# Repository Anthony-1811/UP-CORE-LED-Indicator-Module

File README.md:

# UP CORE LED Indicator module
A quick little PCB to get an LED indicatior on your Up Core. Just send it a string on UART0 on the Up Core.

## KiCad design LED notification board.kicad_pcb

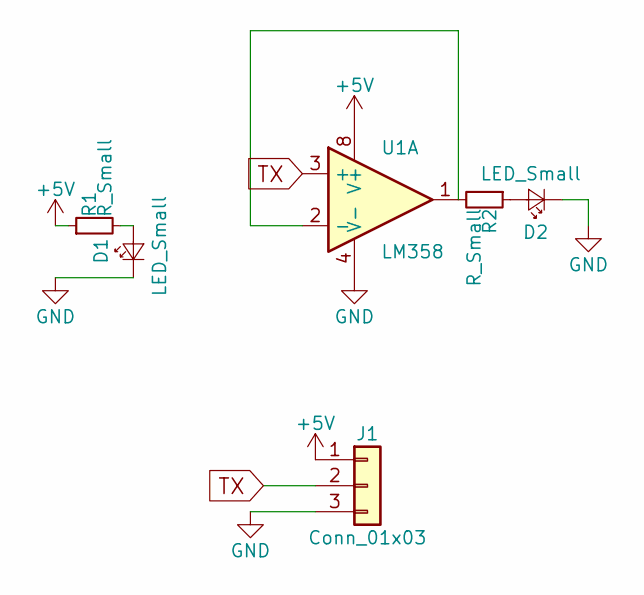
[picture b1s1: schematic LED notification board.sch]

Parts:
D1, D2: LED_Small; LED_0805_HandSoldering
J1: Conn_01x03; JST_GH_SM03B-GHS-TB_03x1.25mm_Angled
R1, R2: R_Small; R_0805_HandSoldering
U1: LM358; SOIC-8_3.9x4.9mm_Pitch1.27mm

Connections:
+5V: J1.1, R1.1, U1.8 (V+)
GND: D1.1 (K), D2.1 (K), J1.3, U1.4 (V-)
unnamed: D1.2 (A), R1.2
unnamed: D2.2 (A), R2.1
unnamed: R2.2, U1.1, U1.2 (-)
TX: J1.2, U1.3 (+)

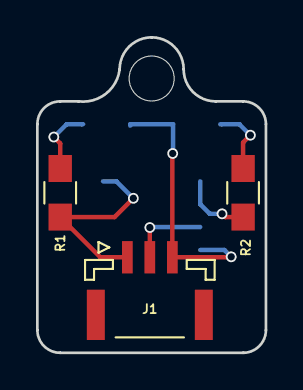
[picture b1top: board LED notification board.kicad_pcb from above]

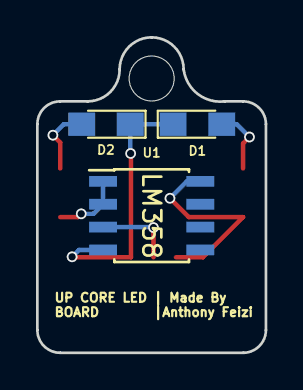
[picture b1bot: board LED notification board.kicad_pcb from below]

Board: 2 copper layers, 12.7 x 17.5 mm, 6 parts (3 on the bottom side), 6 nets.

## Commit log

2019-07-30 Committing files
